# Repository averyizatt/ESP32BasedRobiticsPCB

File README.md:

# ESP32-S3 Robotics Controller PCB

<div align="center">

**A professional-grade, 4-layer ESP32-S3 robotics controller PCB that consolidates motor control, multi-axis sensing, and user interaction into a single, scalable platform.**

</div>

---

## Table of Contents

1. [Board Gallery](#board-gallery)
2. [System Architecture](#system-architecture)
3. [Feature Overview](#feature-overview)
4. [PCB Design](#pcb-design)
   - [Layer Stackup](#layer-stackup)
   - [Signal Integrity](#signal-integrity)
   - [Key Components (BOM Summary)](#key-components-bom-summary)
5. [GPIO Pin Reference](#gpio-pin-reference)
6. [Peripheral Details](#peripheral-details)
   - [Motor Control — DRV8871](#motor-control--drv8871)
   - [Servo Outputs](#servo-outputs)
   - [Ultrasonic Sensors — HC-SR04](#ultrasonic-sensors--hc-sr04)
   - [Hall Effect Sensors](#hall-effect-sensors)
   - [IMU — I2C](#imu--i2c)
   - [SPI Display](#spi-display)
   - [Push Buttons](#push-buttons)
   - [Expansion Header](#expansion-header)
7. [Firmware](#firmware)
   - [Quick Start](#quick-start)
   - [Library Dependencies](#library-dependencies)
   - [Firmware Architecture](#firmware-architecture)
   - [PWM Configuration](#pwm-configuration)
   - [WiFi Access Point & Web Dashboard](#wifi-access-point--web-dashboard)
   - [BLE GATT Server](#ble-gatt-server)
   - [On-Device UI](#on-device-ui)
     - [Main Menu](#main-menu)
     - [Robot Modes](#robot-modes)
     - [Games](#games)
8. [Repository Structure](#repository-structure)
9. [Hardware Files](#hardware-files)
10. [Contributing](#contributing)
11. [License](#license)

---

## Board Gallery

<div align="center">

| PCB Layout (Top) | 3D Render | PCB Back |
|:---:|:---:|:---:|
|  |  |  |

</div>

---

## System Architecture

The diagram below shows how all onboard subsystems connect to the ESP32-S3:

```
                        ┌─────────────────────────────────────┐
                        │           ESP32-S3-WROOM-1           │
                        │     240 MHz Xtensa LX7 Dual-Core     │
                        │     WiFi 802.11 b/g/n  •  BT 5.0    │
                        └───┬───┬───┬───┬───┬───┬───┬───┬─────┘
                            │   │   │   │   │   │   │   │
          ┌─────────────────┘   │   │   │   │   │   │   └──────────────────┐
          │ LEDC PWM            │   │   │   │   │   │ GPIO ISR             │
          ▼                     │   │   │   │   │   ▼                      │
 ┌─────────────────┐            │   │   │   │   │  ┌────────────────┐      │
 │   DRV8871 ×2    │            │   │   │   │   │  │  Hall Sensors  │      │
 │  DC Motor Ctrl  │            │   │   │   │   │  │   ×2 inputs    │      │
 │  (PWM IN1/IN2)  │            │   │   │   │   │  └────────────────┘      │
 └────────┬────────┘            │   │   │   │   │                          │
          │ VM (motor power)    │   │   │   │   │ INPUT_PULLUP             │
          ▼                     │   │   │   │   ▼                          │
    ┌───────────┐               │   │   │   │  ┌──────────────┐            │
    │  Motor ×2 │               │   │   │   │  │  Buttons ×2  │            │
    └───────────┘               │   │   │   │  └──────────────┘            │
                      PWM 50Hz  │   │   │   │                              │
                                ▼   │   │   │ SPI                          │
                       ┌────────────┐  │   ▼                               │
                       │  Servo 1   │  │  ┌──────────────────┐             │
                       └────────────┘  │  │   SPI Display    │             │
                                       │  │  (ST7735 etc.)   │             │
                    HC-SR04 TRIG/ECHO  │  └──────────────────┘             │
                                       ▼                                   │
                           ┌────────────────────┐                          │
                           │  Ultrasonic ×4     │                          │
                           │  (distance 2–400cm)│                          │
                           └────────────────────┘                          │
                                                                           │
          ┌────────────────────────────────────────────────────────────────┘
          │ I2C 400 kHz
          ▼
 ┌──────────────────┐     ┌──────────────────────────────┐
 │  IMU Header      │     │      Power Architecture       │
 │  MPU-6050 /      │     │  VM (7–12 V) ──► DRV8871     │
 │  ICM-42688 etc.  │     │  VM ──► 3.3 V LDO ──► ESP32  │
 └──────────────────┘     │  VM ──► 5 V (servo/sensors)  │
                          └──────────────────────────────┘
```

---

## Feature Overview

| Subsystem | Component | Capability |
|---|---|---|
| **Microcontroller** | ESP32-S3-WROOM-1 | 240 MHz dual-core, WiFi, BT 5.0, 45 GPIOs |
| **Motor Drivers** | 2× DRV8871 | H-bridge, 3.6 A peak, bidirectional DC control |
| **Servo Outputs** | 1 active channel | Servo 1 on GPIO 8; GPIO 9 is used by the menu potentiometer |
| **Ultrasonic Sensors** | 4× HC-SR04 | 2–400 cm range, 15° beam angle |
| **Hall Effect Sensors** | 2× inputs | Wheel speed, pulse counting, position feedback |
| **IMU** | I2C header | MPU-6050, ICM-42688, or any I2C IMU |
| **SPI Display** | ST7735S 160×80 | TFT_eSPI driver, tabbed on-device UI |
| **Push Buttons** | 2× SMD tactile | Top = enter/select, bottom = back/stop; debounced in firmware |
| **Expansion** | GPIO header | GPIO 40, 43, 44, and shared GPIO 48 available for expansion |
| **Power** | LDO + distribution | Onboard 3.3 V regulation, motor VM bus |
| **WiFi AP** | Soft Access Point | SSID `RoboController`, live sensor dashboard |
| **Web Dashboard** | AsyncWebSocket | Tabbed UI: sensors, WiFi scan, BLE radar, drive control |
| **Remote Control** | WebSocket JSON | Browser joystick → motor drive; Servo 1 slider |
| **BLE GATT Server** | NimBLE-Arduino | Sensor notify + motor/servo write characteristics |
| **BLE Scanner** | Passive scan | Detect nearby BLE devices, shown on TFT and dashboard |

---

## PCB Design

### Layer Stackup

The board uses a **4-layer stackup** (1.6 mm total thickness) to provide dedicated power and ground planes, minimizing noise and improving signal integrity:

```
  ┌─────────────────────────────────────────────┐  ← Component side
  │  Layer 1 — F.Cu (Top)                        │  Signal routing + high-current motor traces
  ├─────────────────────────────────────────────┤
  │  Prepreg                                     │
  ├─────────────────────────────────────────────┤
  │  Layer 2 — In1.Cu                            │  Solid GND plane (unbroken)
  ├─────────────────────────────────────────────┤
  │  Core                                        │
  ├─────────────────────────────────────────────┤
  │  Layer 3 — In2.Cu                            │  VM + 3.3 V power distribution
  ├─────────────────────────────────────────────┤
  │  Prepreg                                     │
  ├─────────────────────────────────────────────┤
  │  Layer 4 — B.Cu (Bottom)                     │  Additional signals + local copper pours
  └─────────────────────────────────────────────┘  ← Solder side
```

| Layer | Role | Trace Width |
|---|---|---|
| F.Cu (Top) | Signal routing + high-current motor paths | 0.2 mm signal / 2.0 mm motor VM |
| In1.Cu | Solid GND reference plane | — |
| In2.Cu | VM + 3.3 V power distribution | 0.8 mm+ |
| B.Cu (Bottom) | Additional signals + local copper pours | 0.2 mm signal |

### Signal Integrity

> **Design decisions to ensure reliable operation in a noisy motor-drive environment:**

- **Continuous GND plane** on In1.Cu with stitching vias throughout — minimises return-path inductance for both digital signals and motor switching transients.
- **Wide copper pours** on VM traces and high-current motor paths — rated for DRV8871 peak current with thermal headroom.
- **Local decoupling capacitors** placed directly at each ESP32-S3 power pin and each DRV8871 VCC/VM pin — suppresses switching noise at the source.
- **Physical separation** between sensitive I2C/SPI/UART traces and high-current motor/PWM traces — reduces capacitive and inductive coupling.
- **Short SPI routes** between ESP32-S3 and the display connector — maintains signal integrity at SPI bus speeds.
- **Motor VM routed on power layer (In2.Cu)** — keeps motor current off the signal layers.

### Key Components (BOM Summary)

| Reference | Part | Package | Description |
|---|---|---|---|
| U1 | ESP32-S3-WROOM-1 | SMD module | Main MCU — 240 MHz, WiFi, BT 5.0 |
| U2 | DRV8871 | HSOP-8 | Motor driver — Motor 1 |
| U3 | DRV8871 | HSOP-8 | Motor driver — Motor 2 |
| U4 | 3.3 V LDO | SOT-223 | 3.3 V regulated power for MCU and logic |
| J1–J4 | HC-SR04 headers | 4-pin 2.54 mm | Ultrasonic sensor connectors |
| J5–J6 | Hall sensor headers | 3-pin 2.54 mm | Hall effect sensor connectors |
| J7–J8 | Motor terminals | 2-pin screw terminal | Motor output connections |
| J9 | Expansion header | 8-pin 2.54 mm | Breakout for unused GPIO |
| J10 | Display header | 7-pin 2.54 mm | SPI display connector |
| SW1–SW2 | Tactile switches | SMD | User input buttons used by current firmware |

> Full BOM with part numbers and quantities is available in [`hardware/bom/`](hardware/bom/).

---

## GPIO Pin Reference

| GPIO | Function | Type | Notes |
|---|---|---|---|
| 1 | Hall Sensor 1 | Digital Input | Interrupt-driven pulse counting |
| 2 | Hall Sensor 2 | Digital Input | Interrupt-driven pulse counting |
| 4 | Motor 1 PWM A | LEDC Output | 20 kHz PWM, 8-bit resolution |
| 5 | Motor 1 PWM B | LEDC Output | 20 kHz PWM, 8-bit resolution |
| 6 | Motor 2 PWM A | LEDC Output | 20 kHz PWM, 8-bit resolution |
| 7 | Motor 2 PWM B | LEDC Output | 20 kHz PWM, 8-bit resolution |
| 8 | Servo 1 | PWM Output | 50 Hz via ESP32Servo library |
| 9 | Potentiometer | ADC Input | Main menu scroll / analog control; Servo 2 disabled in firmware |
| 10 | Ultrasonic 1 TRIG | Digital Output | 10 µs trigger pulse |
| 11 | Ultrasonic 1 ECHO | Digital Input | Pulse width → distance |
| 12 | Ultrasonic 2 TRIG | Digital Output | |
| 13 | Ultrasonic 2 ECHO | Digital Input | |
| 14 | Ultrasonic 3 TRIG | Digital Output | |
| 15 | Ultrasonic 3 ECHO | Digital Input | |
| 16 | Ultrasonic 4 TRIG | Digital Output | |
| 17 | Ultrasonic 4 ECHO | Digital Input | |
| 18 | I2C SDA (IMU) | I2C | 400 kHz fast mode |
| 21 | I2C SCL (IMU) | I2C | 400 kHz fast mode |
| 35 | SPI CS | SPI | Active low chip select |
| 36 | SPI DC | Digital Output | Data/Command select |
| 37 | SPI MOSI (Display) | SPI | SDA label on display module |
| 38 | SPI SCLK (Display) | SPI | SCL label on display module |
| 39 | SPI RES | Digital Output | Display reset |
| 41 | Button 1 | Digital Input | `INPUT_PULLUP`, active LOW |
| 42 | Button 2 | Digital Input | `INPUT_PULLUP`, active LOW |
| 48 | Onboard RGB LED | Digital Output | WS2812 / NeoPixel |
| 40, 43, 44 | Expansion Header | GPIO | General purpose — broken out to J9 |

---

## Peripheral Details

### Motor Control — DRV8871

The **DRV8871** is a brushed DC motor driver with an integrated H-bridge, supporting up to **3.6 A peak** current with current-limit protection. Two independent drivers are included for dual-motor operation.

| Motor | PWM A GPIO | PWM B GPIO | LEDC Channel A | LEDC Channel B |
|---|---|---|---|---|
| Motor 1 | 4 | 5 | 0 | 1 |
| Motor 2 | 6 | 7 | 2 | 3 |

**Control truth table:**

| Mode | PWM A | PWM B | Description |
|---|---|---|---|
| Forward | PWM duty | LOW | Speed proportional to duty cycle |
| Reverse | LOW | PWM duty | Speed proportional to duty cycle |
| Coast | LOW | LOW | Motor freewheels (no braking) |
| Brake | HIGH | HIGH | Active braking, motor stops quickly |

```cpp
// Example: drive Motor 1 forward at ~70% speed
motor_set(MotorId::MOTOR1, 180);   // 180/255 ≈ 70%

// Brake Motor 1
motor_brake(MotorId::MOTOR1);

// Coast Motor 2
motor_coast(MotorId::MOTOR2);
```

> **PWM frequency:** 20 kHz (above audible range — eliminates motor whine).  
> **Resolution:** 8-bit (0–255 duty cycle values).

---

### Servo Outputs

Servo 1 outputs a standard 50 Hz RC-servo PWM signal compatible with common hobby servos. Servo 2 hardware exists on GPIO 9, but the current firmware repurposes GPIO 9 as the ADC potentiometer input, so only Servo 1 is active.

| Servo | GPIO | Pulse Width Range |
|---|---|---|
| Servo 1 | 8 | 1000–2000 µs |
| Servo 2 | 9 | Disabled in current firmware; GPIO 9 is `POT_PIN` |

**Pulse width to angle mapping:**

```
1000 µs  ──►  0°   (full left)
1500 µs  ──►  90°  (center / neutral)
2000 µs  ──►  180° (full right)
```

```cpp
// Example: center Servo 1
servo_set_angle(ServoId::SERVO1, 90);
```

---

### Ultrasonic Sensors — HC-SR04

Four **HC-SR04** interfaces provide omnidirectional environmental awareness. Each sensor uses two GPIO pins: one for triggering and one for echo timing.

| Sensor | TRIG GPIO | ECHO GPIO | Max Range | Beam Angle |
|---|---|---|---|---|
| Sensor 1 | 10 | 11 | ~400 cm | ~15° |
| Sensor 2 | 12 | 13 | ~400 cm | ~15° |
| Sensor 3 | 14 | 15 | ~400 cm | ~15° |
| Sensor 4 | 16 | 17 | ~400 cm | ~15° |

**Operating principle:**

```
MCU                    HC-SR04
 │                        │
 │── 10 µs HIGH ─────────►│  TRIG pulse sent
 │                        │── 40 kHz ultrasonic burst ──►
 │                        │                    ◄── echo return
 │◄── pulse width (ECHO) ─│  width ∝ distance
 │
 Distance (cm) = pulse_width_µs × 0.0343 / 2
```

> **Timeout:** 30 ms (~5 m) — sensors beyond range return -1.

---

### Hall Effect Sensors

Two digital Hall effect sensor inputs support wheel speed measurement, odometry, and position feedback. Sensors are read via GPIO interrupts for accurate pulse counting.

| Sensor | GPIO | Mode |
|---|---|---|
| Hall 1 | 1 | Interrupt (rising edge) |
| Hall 2 | 2 | Interrupt (rising edge) |

```cpp
// Example: read rotational speed
float pps1 = hall_get_pulses_per_second(1);   // pulses per second
float pps2 = hall_get_pulses_per_second(2);
```

To calculate RPM, divide pulses per second by the number of magnet poles on the wheel.

---

### IMU — I2C

A dedicated I2C header supports any standard I2C IMU module.

| Signal | GPIO | Frequency |
|---|---|---|
| SDA | 18 | 400 kHz (fast mode) |
| SCL | 21 | 400 kHz (fast mode) |

**Compatible IMUs (non-exhaustive):**

| Part | Axes | Interface |
|---|---|---|
| MPU-6050 | 6-axis (accel + gyro) | I2C (0x68 / 0x69) |
| ICM-42688 | 6-axis (accel + gyro) | I2C / SPI |
| BNO055 | 9-axis (+ magnetometer, fusion) | I2C (0x28 / 0x29) |
| LSM6DSO | 6-axis | I2C / SPI |

```cpp
// Example: read IMU data
ImuData imu;
if (imu_read(imu)) {
    // accel in g, gyro in °/s
    Serial.printf("ax=%.2f  ay=%.2f  az=%.2f\n",
                  imu.accel_x, imu.accel_y, imu.accel_z);
}
```

---

### SPI Display

An SPI display connector supports ST7735, ST7789, ILI9341, or any SPI display with a compatible driver.

| Signal | GPIO | Function |
|---|---|---|
| MOSI (SDA) | 37 | Data to display |
| SCLK (SCL) | 38 | SPI clock |
| CS | 35 | Chip select (active LOW) |
| DC | 36 | Data / Command select |
| RES | 39 | Hardware reset |

The firmware uses **TFT_eSPI** for hardware-accelerated graphics and text rendering on the ST7735S 160×80 display. A custom colour palette and tabbed on-device UI are implemented in `display.h/cpp` and `ui.h/cpp`.

---

### Push Buttons

The current firmware uses two tactile buttons. Firmware enables `INPUT_PULLUP`, treats `LOW` as pressed, and applies software debouncing with `BUTTON_DEBOUNCE_MS` (default 20 ms).

| Button | GPIO | UI Role |
|---|---|---|
| Top button / Button 1 | 41 | Enter, open, select, primary action |
| Bottom button / Button 2 | 42 | Back, stop, return to menu |

GPIO 47 / Button 3 is not populated or used by the current 2-button UI.

```cpp
// Example: detect button press events
buttons_update();   // call every loop iteration

if (nav_enter_just_pressed()) {
    // top button pressed
}

if (nav_back_just_pressed()) {
    // bottom button pressed
}
```

---

### Expansion Header

Several GPIO pins are broken out on **J9** for custom peripherals, additional sensors, or future expansion. Some physical header pins are shared with active firmware functions, so check `config.h` before reusing them.

| Header Pin | GPIO | Notes |
|---|---|---|
| 1 | 37 | SPI display MOSI in current firmware |
| 2 | 38 | SPI display SCLK in current firmware |
| 3 | 40 | General purpose |
| 4 | 43 | UART0 TX (also used for USB CDC) |
| 5 | 44 | UART0 RX (also used for USB CDC) |
| 6 | 48 | Onboard RGB LED / WS2812 |
| 7 | 3.3 V | Power rail |
| 8 | GND | Ground |

> GPIO 43 and 44 are the default UART0 pins and can be used for serial communication with external devices.

---

## Firmware

### Quick Start

```bash
# 1. Clone the repository
git clone https://github.com/averyizatt/ESP32BasedRobiticsPCB.git

# 2. Open in PlatformIO (recommended)
#    File → Open Folder → ESP32BasedRobiticsPCB
#    PlatformIO auto-resolves all lib_deps from platformio.ini

# 3. Build
pio run --environment esp32s3

# 4. Upload
pio run --target upload --environment esp32s3
```

1. Install **PlatformIO** (VS Code extension or CLI)
2. Open the repo root as the workspace
3. PlatformIO resolves all library dependencies automatically from `platformio.ini`
4. Select the **esp32s3** environment, build, and upload
5. After boot, connect to WiFi SSID `RoboController` (password `robot1234`) and navigate to `http://192.168.4.1`

### Library Dependencies

All dependencies are declared in `platformio.ini` and resolved automatically by PlatformIO. For manual Arduino IDE installs use the Library Manager names below.

| Library | Version | Purpose |
|---|---|---|
| `madhephaestus/ESP32Servo` | ^3.0.6 | RC servo 50 Hz PWM |
| `bodmer/TFT_eSPI` | ^2.5.43 | ST7735S SPI display driver + graphics |
| `ESP32Async/AsyncTCP` | ^3.3.2 | Async TCP foundation for web server |
| `ESP32Async/ESPAsyncWebServer` | ^3.7.4 | Async HTTP + WebSocket server |
| `h2zero/NimBLE-Arduino` | ^1.4.3 | BLE stack (GATT server + scanning) |
| `Wire` | built-in | I2C for IMU |
| `WiFi` | built-in | Soft AP + network scanning |

> **TFT_eSPI user config:** The library reads pin assignments from `User_Setup.h`. Ensure the file in your PlatformIO build includes the ST7735S settings matching `config.h` (MOSI=37, SCLK=38, CS=35, DC=36, RST=39).

### Firmware Architecture

The firmware is organized as a set of independent peripheral modules — each with its own header and source file — all coordinated from `main.cpp`:

```
ESP32RoboticsController/
├── main.cpp                         ← setup() + loop() entry point
├── config.h                         ← All pin definitions and tuning constants
│
├── motors.h / motors.cpp            ← DRV8871 LEDC-based motor control
├── servos.h / servos.cpp            ← RC servo PWM control
├── ultrasonics.h / ultrasonics.cpp  ← HC-SR04 distance measurement
├── hall_sensors.h / hall_sensors.cpp← Interrupt-based pulse counting
├── imu.h / imu.cpp                  ← I2C IMU read abstraction (MPU-6050)
├── buttons.h / buttons.cpp          ← Debounced button state machine
├── led.h / led.cpp                  ← Onboard LED control
├── pot.h / pot.cpp                  ← Potentiometer / ADC helper
│
├── display.h / display.cpp          ← TFT_eSPI display abstraction + colour palette
├── ui.h / ui.cpp                    ← On-device tabbed UI state machine
├── games.h / games.cpp              ← Mini-game / demo logic
├── autonomous_modes.h / autonomous_modes.cpp
│                                      ← Autonomous driving state machine
├── robot_modes.h / robot_modes.cpp  ← Robot mode selector + active-mode runner
│
└── wifi_server.h / wifi_server.cpp  ← WiFi soft AP, AsyncWebServer, WebSocket push,
                                        BLE GATT server, WiFi/BLE scanner helpers
```

All pin assignments and tunable parameters are centralized in `config.h` — adapting the firmware to a modified hardware revision only requires editing that single file.

### PWM Configuration

Motor PWM is generated using the ESP32-S3's **LEDC peripheral**, which provides hardware-timed PWM independent of the CPU:

| Parameter | Value | Notes |
|---|---|---|
| Frequency | 20 kHz | Above human hearing — eliminates audible motor whine |
| Resolution | 8-bit | 0–255 duty cycle values |
| Channels | 4 (0–3) | One per motor H-bridge input |

---

### WiFi Access Point & Web Dashboard

The firmware starts a **soft Access Point** on boot. Connect any browser-capable device to control and monitor the robot.

| Setting | Value |
|---|---|
| SSID | `RoboController` |
| Password | `robot1234` |
| IP Address | `192.168.4.1` |
| WebSocket | `ws://192.168.4.1/ws` |

The dashboard is a single-page app served from PROGMEM with four tabs:

| Tab | Contents |
|---|---|
| **Sensors** | Live IMU (accel + gyro axis bars), ultrasonic proximity radar, heap gauge, hall encoder counts, button tiles, uptime |
| **WiFi Scanner** | Scan nearby networks — SSID, signal strength bar, channel, security badge |
| **BLE Radar** | Scan for BLE devices — name, RSSI, MAC address |
| **Control** | Virtual joystick (touch + mouse), Servo 1 control, emergency stop, command log |

Sensor data is pushed over **WebSocket** (no polling) at a configurable interval (`WIFI_WS_PUSH_MS`, default 200 ms).

#### REST Endpoints

| Endpoint | Method | Response |
|---|---|---|
| `/` | GET | Full HTML dashboard |
| `/api/scan` | GET | JSON array of nearby WiFi networks |
| `/api/ble` | GET | JSON array of scanned BLE devices (~4 s scan) |

#### WebSocket Commands (browser → robot)

The robot accepts inbound JSON commands over the same WebSocket connection:

```json
// Drive both motors (speed: -255 to +255)
{ "t": "drive", "l": 200, "r": -150 }

// Set Servo 1 angle (angle: 0–180°)
{ "t": "servo", "id": 1, "angle": 90 }

// Emergency stop — coasts both motors
{ "t": "stop" }
```

---

### BLE GATT Server

The firmware advertises a custom BLE GATT service alongside the WiFi AP — connect from **nRF Connect**, **LightBlue**, or any GATT-capable app.

| Item | UUID | Properties | Format |
|---|---|---|---|
| Service | `AB12` | — | — |
| Sensor Notify | `AA13` | Read + Notify | Compact JSON: accel, gyro, ultrasonic |
| Motor Write | `AA14` | Write | `l:<speed>,r:<speed>` e.g. `l:200,r:-150` |
| Servo Write | `AA15` | Write | `<id>:<angle>` e.g. `1:90` |

The sensor characteristic sends a live data notification every **500 ms** when a central is connected:

```json
{"ax":0.01,"ay":-0.03,"az":9.81,"gx":0.2,"gy":-0.1,"gz":0.0,"u":[45.2,120.0,-1.0,88.4]}
```

(`u` values are ultrasonic distances in cm; `-1` = no echo / out of range)

---

### On-Device UI

A tabbed menu system runs on the 160×80 TFT display. Navigation uses two push buttons and the onboard potentiometer. An auto-idle screensaver activates after 20 seconds of inactivity.

**Navigation:**
- **Top button / GPIO 41** — enter, open, select, or primary action
- **Bottom button / GPIO 42** — back, stop active mode, or return to menu
- **Potentiometer** — main menu selection and analog controls inside demos/games

In the main menu the potentiometer maps directly across the list: pot minimum selects the first item, and pot maximum selects the last item. It does not wrap around.

#### Main Menu

| Menu Item | Screen | Description |
|---|---|---|
| Sensors | Live readout | All sensor values: ultrasonic distances, hall encoder counts, button states, uptime |
| IMU Data | Live readout | Accelerometer (X/Y/Z in g) and gyroscope (X/Y/Z in °/s) with temperature |
| Tilt Demo | Animation | Graphical liquid-level tilt visualiser driven by IMU pitch/roll |
| Motors | Live readout | Current motor speed and direction for both motor channels |
| Ultrasonic | Radar demo | Real-time 4-direction proximity radar on TFT |
| Hall Demo | Live readout | Wheel pulse counts and pulses-per-second for both encoder channels |
| Servo Demo | Manual servo control | Servo 1 starts at 90°; moving the pot commands 0–180° |
| System | Info screen | Firmware uptime, heap usage, CPU frequency, chip info |
| Games | Sub-menu | Arcade game launcher (see Games section below) |
| Robot Modes | Sub-menu | Autonomous / RC mode launcher; bottom button stops active mode |
| WiFi Info | Info screen | AP SSID, password, IP address, connected client count |
| WiFi Scan | Scanner | Nearby WiFi networks with RSSI bars; pot scrolls list |
| BLE Radar | Scanner | Nearby BLE devices with RSSI bars; 4-second active scan |

#### Robot Modes

The Robot Modes menu starts the autonomous-mode engine from the display UI. The top button starts the highlighted mode, the bottom button exits the menu, and while a mode is running the bottom button stops the mode and returns to the Robot Modes list.

| Mode | Description |
|---|---|
| RC Control | Xbox BLE joystick / tank-drive control |
| UART Control | UART-commanded forward control |
| Socket Ctrl | Socket motor pass-through |
| Autonomous | Advanced state-machine mode |
| Simple Auto | PID forward motion with recovery behavior |
| Wall Follow | Left-hand PID wall follower |
| Premap Nav | Map-seeded autonomous navigation |

#### Games

The Games menu launches a sub-menu with three sprite-rendered arcade games. All games use a **full-screen off-screen framebuffer** (TFT_eSprite) pushed via DMA for zero-flicker 40 fps rendering. Win/loss statistics are stored in RAM for the session and displayed in the game menu next to each title.

---

##### Snake

> Classic snake — eat food to grow, avoid your own tail. Walls wrap.

| Detail | Value |
|---|---|
| Grid | 40 × 14 cells (4 px each) |
| Win condition | Score 20 food pieces |
| Controls | Potentiometer zones or top button to turn; bottom returns from game-over/menu screens |
| Speed | Increases with score (160 ms → 50 ms minimum tick) |
| Visual effects | Gradient tail fade, pulsing food, particle burst on eat/death, screen shake on collision |

---

##### Pong

> Single-player Pong — keep the ball alive and score paddle hits.

| Detail | Value |
|---|---|
| Win condition | 10 paddle hits |
| Lives | 3 |
| Controls | Potentiometer maps directly to paddle Y position; top button retries from game-over |
| Difficulty | Ball speed +0.15 per hit, capped at 5.5 px/frame |
| Visual effects | 6-frame ball trail, glowing neon paddle, particle bursts on wall/paddle hits, screen shake on miss |

---

##### Asteroids

> Side-scrolling asteroid dodge — survive as long as possible.

| Detail | Value |
|---|---|
| Win condition | Survive 1500 score ticks (~37 s at 40 fps) |
| Lives | 3 |
| Controls | Potentiometer steers ship Y (smoothed); top button retries from game-over |
| Difficulty | Rock speed 2.2 → 5.0 px/frame; spawn interval 1100 → 350 ms |
| Visual effects | 3-layer parallax starfield, procedural 8-vertex asteroid shapes, thruster flame + exhaust particles, invulnerability blink after hit, screen shake on collision |

---

All three games share:
- **Particle system** — 24-particle pool with gravity and colour fade, reused across all effects
- **Screen shake** — configurable intensity applied as DMA push offset
- **Session W/L stats** — shown in the games menu and on the game-over screen
- **LED feedback** — green on score/win, red on death/hit, blue on game start

---

## Repository Structure

```
ESP32BasedRobiticsPCB/
│
├── platformio.ini                     ← PlatformIO project config + lib_deps
│
├── firmware/
│   └── ESP32RoboticsController/
│       ├── main.cpp                   ← setup() + loop() entry point
│       ├── config.h                   ← Pin map & constants (start here)
│       ├── motors.h / motors.cpp      ← DRV8871 LEDC motor control
│       ├── servos.h / servos.cpp      ← RC servo PWM
│       ├── ultrasonics.h / ultrasonics.cpp  ← HC-SR04 distance
│       ├── hall_sensors.h / hall_sensors.cpp← Interrupt pulse counting
│       ├── imu.h / imu.cpp            ← MPU-6050 I2C abstraction
│       ├── buttons.h / buttons.cpp    ← Debounced buttons
│       ├── led.h / led.cpp            ← Onboard LED
│       ├── pot.h / pot.cpp            ← ADC potentiometer
│       ├── display.h / display.cpp    ← TFT_eSPI wrapper + colour palette
│       ├── ui.h / ui.cpp              ← On-device tabbed UI state machine
│       ├── games.h / games.cpp        ← Demo / mini-game logic
│       ├── autonomous_modes.h / autonomous_modes.cpp
│       │                                ← Autonomous driving state machine
│       ├── robot_modes.h / robot_modes.cpp
│       │                                ← Robot mode selector + active-mode runner
│       └── wifi_server.h / wifi_server.cpp  ← WiFi AP, web dashboard,
│                                              WebSocket, BLE GATT
│
└── hardware/                          # KiCad 7 PCB design files
    ├── kicadProject/
    │   ├── Tank.kicad_pro
    │   ├── Tank.kicad_sch
    │   ├── Tank.kicad_pcb
    │   └── Tank.step
    ├── gerbers/                        ← Fabrication-ready Gerber files
    └── bom/                            ← Bill of materials (bom.csv)
```

---

## Hardware Files

KiCad design files are in the [`hardware/`](hardware/) directory.

1. Install [KiCad 7](https://www.kicad.org/download/) or later
2. Open `hardware/kicadProject/Tank.kicad_pro`
3. The schematic opens in **Eeschema**; the PCB layout opens in **Pcbnew**

**Generating Gerbers for fabrication** (Pcbnew → File → Fabrication Outputs → Gerbers):

| File | Layer |
|---|---|
| `*-F_Cu.gbr` | Top copper |
| `*-In1_Cu.gbr` | Inner GND plane |
| `*-In2_Cu.gbr` | Inner power plane |
| `*-B_Cu.gbr` | Bottom copper |
| `*-F_SilkS.gbr` / `*-B_SilkS.gbr` | Silkscreen |
| `*-F_Mask.gbr` / `*-B_Mask.gbr` | Solder mask |
| `*-F_Paste.gbr` | Solder paste |
| `*-Edge_Cuts.gbr` | Board outline |
| `*.drl` | Drill file (Excellon) |

Pre-generated Gerber files are available in [`hardware/gerbers/`](hardware/gerbers/).

---

## Contributing

Contributions are welcome! To contribute:

1. Fork the repository
2. Create a feature branch (`git checkout -b feature/my-improvement`)
3. Commit your changes with a clear message
4. Open a pull request describing what you changed and why

**For hardware changes:** please include updated Gerber files and a brief description of the PCB modification.  
**For firmware changes:** please test on hardware before submitting.

---

## License

MIT License — see [LICENSE](LICENSE) for details.

---

<div align="center">

Made with ❤️ for the robotics community

</div>

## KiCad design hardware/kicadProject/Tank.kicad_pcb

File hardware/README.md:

# Hardware — KiCad PCB Design Files

This directory contains the KiCad 7 project for the ESP32-S3 Robotics Controller PCB.

## Files

| File | Description |
|---|---|
| `ESP32RoboticsController.kicad_pro` | KiCad project file |
| `ESP32RoboticsController.kicad_sch` | Schematic |
| `ESP32RoboticsController.kicad_pcb` | PCB layout |
| `ESP32RoboticsController.kicad_dru` | Design rules |
| `fp-lib-table` | Footprint library table |
| `sym-lib-table` | Symbol library table |
| `gerbers/` | Fabrication-ready Gerber files |
| `bom/` | Bill of materials |
| `datasheets/` | Component datasheets |

## PCB Stackup

| Layer | Role |
|---|---|
| F.Cu (Top) | Signal routing + high-current paths |
| In1.Cu | Solid GND plane |
| In2.Cu | VM + regulated power distribution |
| B.Cu (Bottom) | Additional signals + local pours |

## Key Components

| Reference | Part | Package |
|---|---|---|
| U1 | ESP32-S3-WROOM-1 | SMD module |
| U2 | DRV8871 (Motor 1) | HSOP-8 |
| U3 | DRV8871 (Motor 2) | HSOP-8 |
| U4 | 3.3 V LDO regulator | SOT-223 |
| J1–J4 | Ultrasonic sensor headers | 4-pin 2.54 mm |
| J5–J6 | Hall sensor headers | 3-pin 2.54 mm |
| J7–J8 | Motor terminals | 2-pin screw terminal |
| J9 | Expansion GPIO header | 8-pin 2.54 mm |
| J10 | SPI display header | 7-pin 2.54 mm |
| SW1–SW3 | Push buttons | SMD tactile |
| DSP1 | SPI display (e.g., ST7735) | connector |

## Opening the Project

1. Install [KiCad 7](https://www.kicad.org/download/)
2. Open `ESP32RoboticsController.kicad_pro`
3. The schematic opens in Eeschema; the PCB opens in Pcbnew

## Generating Gerbers

In Pcbnew: **File → Fabrication Outputs → Gerbers**

Recommended layers for 4-layer fabrication:
- F.Cu, In1.Cu, In2.Cu, B.Cu
- F.SilkS, B.SilkS
- F.Mask, B.Mask
- Edge.Cuts
- F.Paste

## Design Rules

- Min trace width: 0.2 mm (signal), 0.8 mm (power), 2.0 mm (motor VM)
- Min via drill: 0.3 mm
- Min clearance: 0.2 mm
- Board thickness: 1.6 mm

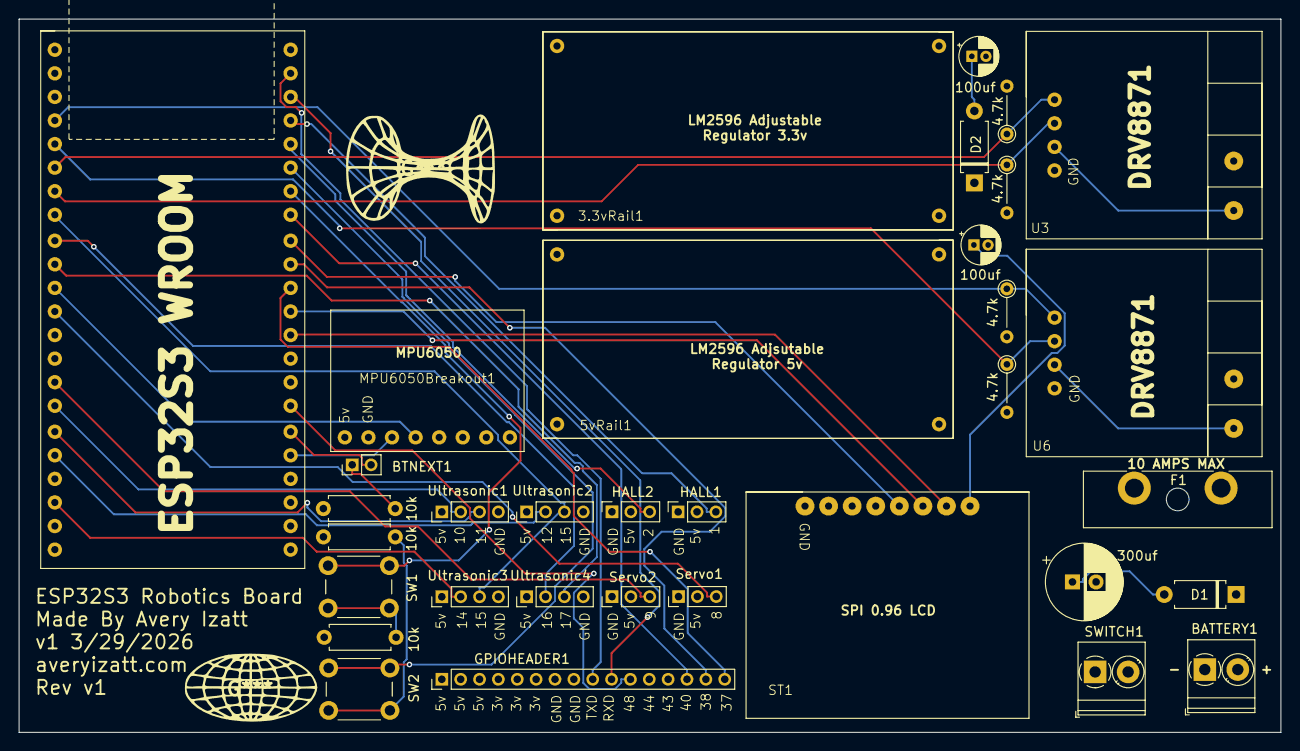
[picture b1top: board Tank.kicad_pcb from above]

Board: 4 copper layers, 133.8 x 75.6 mm, 34 parts (0 on the bottom side), 40 nets.

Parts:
3.3vRail1, 5vRail1: LM2596Adj
4.7k, 4.7k#2, 4.7k#3, 4.7k#4: R; R_Axial_DIN0204_L3.6mm_D1.6mm_P5.08mm_Vertical
10k, 10k#2, 10k#3: R; R_Axial_DIN0207_L6.3mm_D2.5mm_P7.62mm_Horizontal
100uf, 100uf#2: C_Polarized; CP_Radial_D4.0mm_P1.50mm
300uf: C_Polarized; CP_Radial_D8.0mm_P2.50mm
BATTERY1: Screw_Terminal_2_P3.50mm; TerminalBlock_Phoenix_PT-1,5-2-3.5-H_1x02_P3.50mm_Horizontal
BTNEXT1: Conn_01x02_Pin; PinHeader_1x02_P2.00mm_Vertical
D1, D2: D; D_A-405_P7.62mm_Horizontal
ESP32-S3WROOM45Pin1: ESP32S3
F1: Fuse; Fuseholder_Blade_ATO_Littelfuse_Pudenz_2_Pin
GPIOHEADER1: Conn_01x16_Pin; PinHeader_1x16_P2.00mm_Vertical
HALL1, HALL2: Conn_01x03_Pin; PinSocket_1x03_P2.00mm_Vertical
MPU6050Breakout1: MPU6050
ST1: SPI 0.96 LCD
SW1, SW2: Push_Button; SW_PUSH_6mm
SWITCH1: Screw_Terminal_2_P3.50mm; TerminalBlock_Phoenix_PT-1,5-2-3.5-H_1x02_P3.50mm_Horizontal
Servo1, Servo2: Conn_01x03_Pin; PinHeader_1x03_P2.00mm_Vertical
U3, U6: DRV8871
Ultrasonic1, Ultrasonic2, Ultrasonic3, Ultrasonic4: Conn_01x04_Pin; PinHeader_1x04_P2.00mm_Vertical

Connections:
3.3V: 3.3vRail1.3 (OUT+), 100uf.1, ESP32-S3WROOM45Pin1.1 (3.3v), ESP32-S3WROOM45Pin1.2 (3.3v), GPIOHEADER1.4, GPIOHEADER1.5, GPIOHEADER1.6, ST1.2 (VCC), ST1.8 (BLK)
5V: 5vRail1.3 (OUT+), 100uf#2.1, D2.2 (A), GPIOHEADER1.1, GPIOHEADER1.2, GPIOHEADER1.3, HALL1.2, HALL2.2, MPU6050Breakout1.1 (VCC), Servo1.2, Servo2.2, Ultrasonic1.1, Ultrasonic2.1, Ultrasonic3.1, Ultrasonic4.1
GND: 3.3vRail1.2 (IN-), 3.3vRail1.4 (OUT-), 4.7k.2, 4.7k#2.2, 4.7k#3.2, 4.7k#4.2, 5vRail1.2 (IN-), 5vRail1.4 (OUT-), 10k.2, 10k#2.2, 10k#3.2, 100uf.2, 100uf#2.2, 300uf.2, BATTERY1.1, ESP32-S3WROOM45Pin1.22 (GND), ESP32-S3WROOM45Pin1.23 (GND), ESP32-S3WROOM45Pin1.43 (GND), ESP32-S3WROOM45Pin1.44 (GND), GPIOHEADER1.7, GPIOHEADER1.8, HALL1.1, HALL2.1, MPU6050Breakout1.2 (GND), ST1.1 (GND), Servo1.1, Servo2.1, U3.2 (GND), U3.6 (GND), U6.2 (GND), U6.6 (GND), Ultrasonic1.4, Ultrasonic2.4, Ultrasonic3.4, Ultrasonic4.4
GPIO1: ESP32-S3WROOM45Pin1.26 (GPIO1), HALL1.3
GPIO2: ESP32-S3WROOM45Pin1.27 (GPIO2), HALL2.3
GPIO4: 4.7k#4.1, ESP32-S3WROOM45Pin1.4 (GPIO4), U6.3 (IN1)
GPIO5: 4.7k#2.1, ESP32-S3WROOM45Pin1.5 (GPIO5), U6.4 (IN2)
GPIO6: 4.7k.1, ESP32-S3WROOM45Pin1.6 (GPIO6), U3.3 (IN1)
GPIO7: 4.7k#3.1, ESP32-S3WROOM45Pin1.7 (GPIO7), U3.4 (IN2)
GPIO8: ESP32-S3WROOM45Pin1.12 (GPIO8), Servo1.3
GPIO9: ESP32-S3WROOM45Pin1.15 (GPIO9), Servo2.3
GPIO10: ESP32-S3WROOM45Pin1.16 (GPIO10), Ultrasonic1.2
GPIO11: ESP32-S3WROOM45Pin1.17 (GPIO11), Ultrasonic1.3
GPIO12: ESP32-S3WROOM45Pin1.18 (GPIO12), Ultrasonic2.2
GPIO14: ESP32-S3WROOM45Pin1.20 (GPIO14), Ultrasonic3.2
GPIO15: ESP32-S3WROOM45Pin1.8 (GPIO15), Ultrasonic2.3, Ultrasonic3.3
GPIO16: ESP32-S3WROOM45Pin1.9 (GPIO16), Ultrasonic4.2
GPIO17: ESP32-S3WROOM45Pin1.10 (GPIO17), Ultrasonic4.3
GPIO18: ESP32-S3WROOM45Pin1.11 (GPIO18), MPU6050Breakout1.4 (SDA)
GPIO21: ESP32-S3WROOM45Pin1.40 (GPIO21), MPU6050Breakout1.3 (SCL)
GPIO35: ESP32-S3WROOM45Pin1.35 (GPIO35), ST1.7 (CS)
GPIO36: ESP32-S3WROOM45Pin1.34 (GPIO36), ST1.6 (DC)
GPIO37: ESP32-S3WROOM45Pin1.33 (GPIO37), GPIOHEADER1.16
GPIO38: ESP32-S3WROOM45Pin1.32 (GPIO38), GPIOHEADER1.15
GPIO39: ESP32-S3WROOM45Pin1.31 (GPIO39), ST1.5 (RES)
GPIO40: ESP32-S3WROOM45Pin1.30 (GPIO40), GPIOHEADER1.14
GPIO41: ESP32-S3WROOM45Pin1.29 (GPIO41), SW1.1
GPIO42: ESP32-S3WROOM45Pin1.28 (GPIO42), SW2.1
GPIO47: BTNEXT1.2, ESP32-S3WROOM45Pin1.39 (GPIO47)
GPIO48: ESP32-S3WROOM45Pin1.38 (GPIO48), GPIOHEADER1.11
unnamed: 3.3vRail1.1 (IN+), D2.1 (K)
unnamed: BATTERY1.2, F1.1
unnamed: 10k.1, BTNEXT1.1
unnamed: 300uf.1, D1.2 (A), SWITCH1.2
unnamed: F1.2, SWITCH1.1
unnamed: 10k#2.1, SW1.2
unnamed: 10k#3.1, SW2.2
RXD: ESP32-S3WROOM45Pin1.25 (RXD), GPIOHEADER1.10
TXD: ESP32-S3WROOM45Pin1.24 (TXD), GPIOHEADER1.9
VM: 5vRail1.1 (IN+), D1.1 (K), U3.1 (VM), U3.5 (VM), U6.1 (VM), U6.5 (VM)

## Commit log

2026-04-03 Initial plan
2026-04-03 Create initial PCB project starter base with firmware and hardware structure
    Agent-Logs-Url: https://github.com/averyizatt/ESP32BasedRobiticsPCB/sessions/d9f3cad1-dcbc-4a22-a679-e6851b55c6f7
2026-04-03 Add PCB images to README
    Agent-Logs-Url: https://github.com/averyizatt/ESP32BasedRobiticsPCB/sessions/4e5fb9b7-d99e-4026-89df-6d83c5fe2d7e
2026-04-03 docs: significantly enhance README with badges, ToC, architecture diagram, and deeper technical detail
    Agent-Logs-Url: https://github.com/averyizatt/ESP32BasedRobiticsPCB/sessions/25968c5d-c666-468f-8afb-e7f4a778fa04
2026-04-03 Kicad project files for the Tank project. These files include the PCB layout, schematic, and related resources. The project is organized in a way that allows for easy navigation and modification of t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
2026-04-18 DIsplay changes + Games!
2026-04-24 ESP Board Updates
2026-04-27 UI Fixes
